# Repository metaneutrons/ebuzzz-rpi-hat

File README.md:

# eBuzzz adapter, an eBus to serial adapter

An eBus adapter, to convert eBus signal levels to serial level for a serial to USB converter (Works with CP2102)

# Manufacturing

Manufacturing in the `manufacturing` folder are made for JLCPCB, you may need to tweak them for other manufacturers.

# Software

The eBus protocol can be connected to with [ebusd](https://github.com/john30/ebusd). If you happen to use Home Assistant you can also connect ebusd to your Home Assistant.

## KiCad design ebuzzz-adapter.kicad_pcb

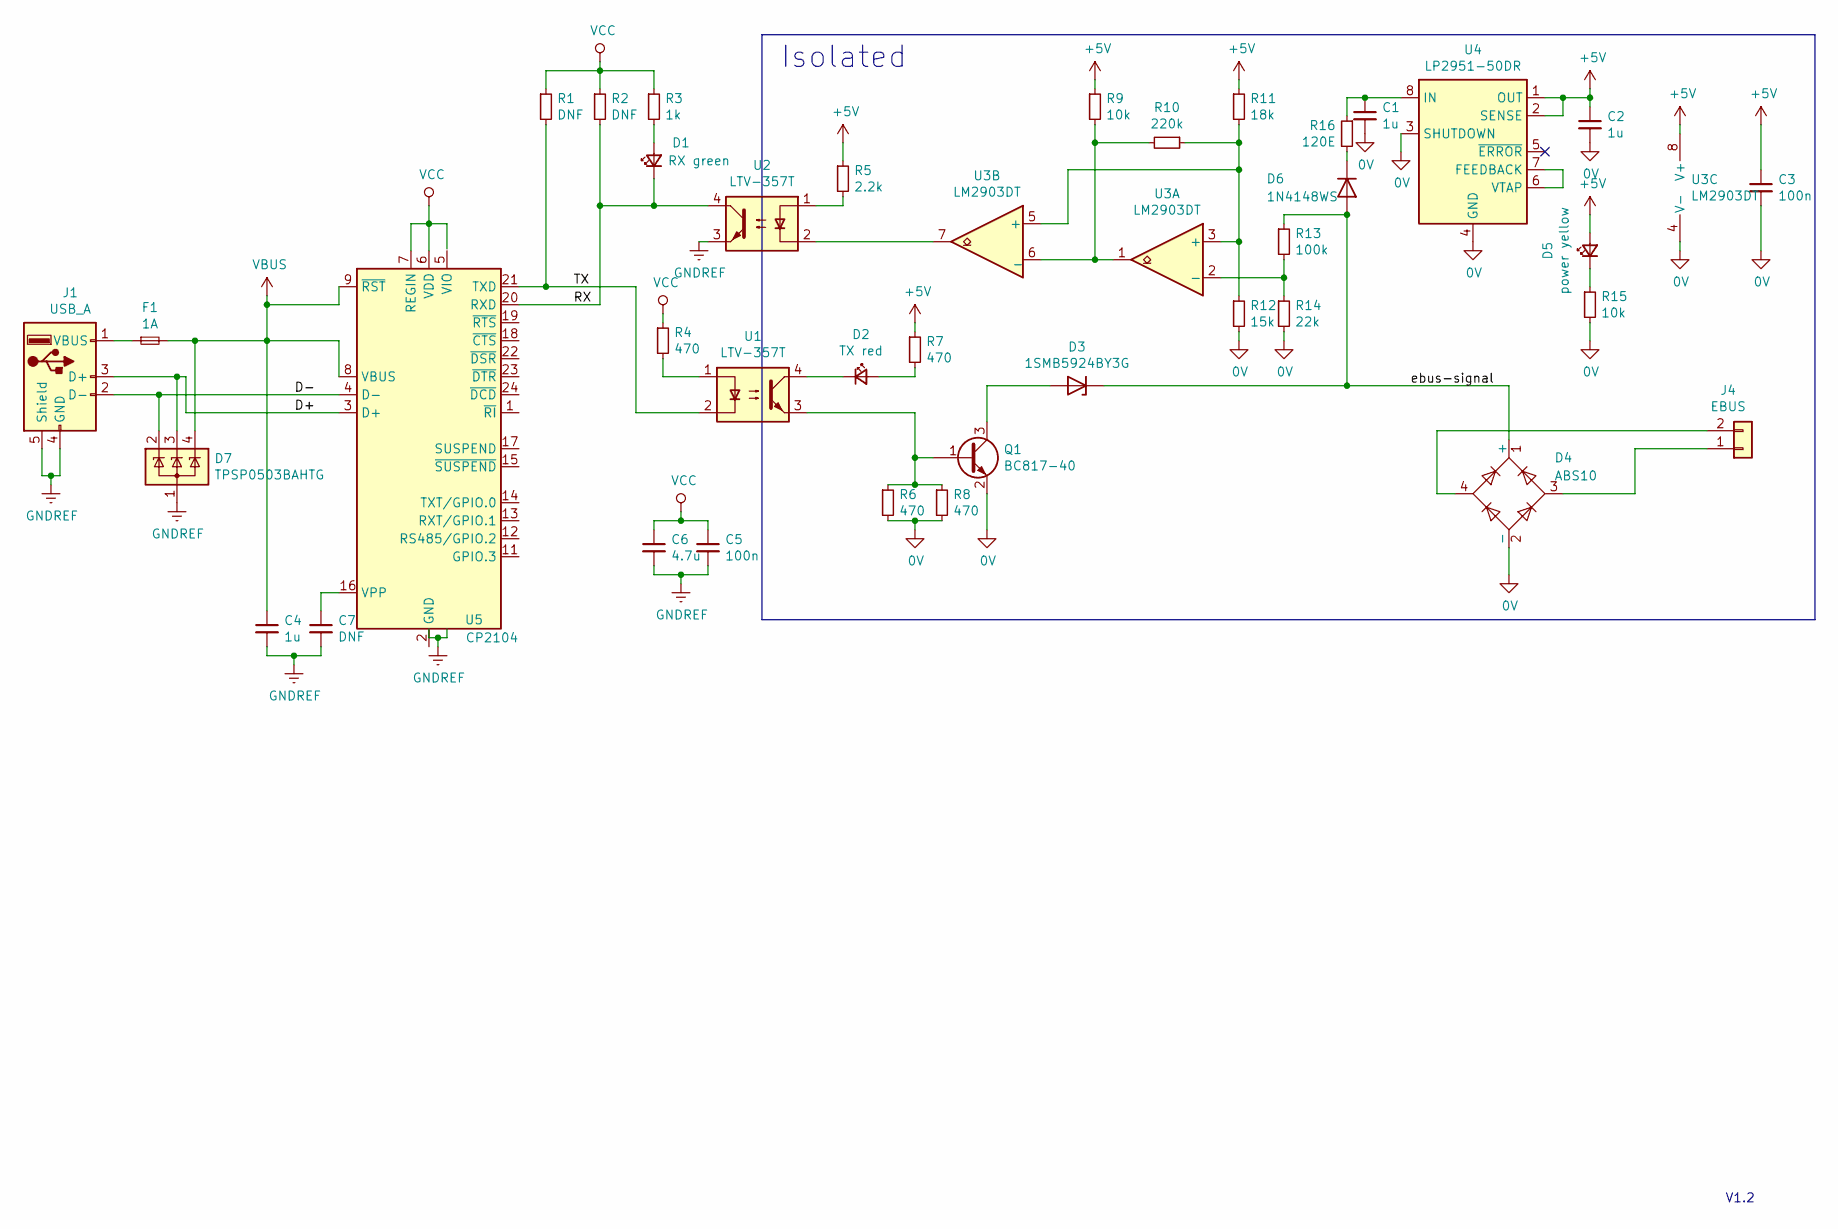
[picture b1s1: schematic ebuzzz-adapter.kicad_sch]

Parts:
C1, C2, C4: 1u; C_0805_2012Metric; LCSC C28323
C3, C5: 100n; C_0805_2012Metric; LCSC C49678
C6: 4.7u; C_0805_2012Metric; LCSC C1779
C7: DNF; C_0805_2012Metric
D1: RX green; LED_0805_2012Metric; LCSC C2297
D2: TX red; LED_0805_2012Metric; LCSC C84256
D3: 1SMB5924BY3G; D_SMA; Farnell 1611267
D4: ABS10; Diode_Bridge_Diotec_ABS; Farnell 3127182
D5: power yellow; LED_0805_2012Metric; LCSC C2296
D6: 1N4148WS; D_SOD-323; Farnell 2675148
D7: TPSP0503BAHTG; SOT-143; LCSC C2682275
F1: 1A; Fuse_1206_3216Metric; LCSC C182308
J1: USB_A; XKB_Connectivity_U217-041N-4BV81; LCSC C319178
J4: EBUS; PhoenixContact_MC_1,5_2-G-3.81_1x02_P3.81mm_Horizontal; LCSC C69811
Q1: BC817-40; SOT-23; Farnell 1798081
R1, R2: DNF; R_0805_2012Metric
R3: 1k; R_0805_2012Metric; LCSC C17513
R4, R6, R7, R8: 470; R_0805_2012Metric; LCSC C17710
R5: 2.2k; R_0805_2012Metric; LCSC C17520
R9, R15: 10k; R_0805_2012Metric; LCSC C17414
R10: 220k; R_0805_2012Metric; LCSC C17556
R11: 18k; R_0805_2012Metric; LCSC C17506
R12: 15k; R_0805_2012Metric; LCSC C17475
R13: 100k; R_0805_2012Metric; LCSC C17407
R14: 22k; R_0805_2012Metric; LCSC C17560
R16: 120E; R_0805_2012Metric; LCSC C17437
U1, U2: LTV-357T; SO-4_4.4x3.6mm_P2.54mm; LCSC C33068
U3: LM2903DT; SOIC-8_3.9x4.9mm_P1.27mm; Farnell 2382615
U4: LP2951-50DR; SOIC-8_3.9x4.9mm_P1.27mm; Farnell 1755065
U5: CP2104; QFN-24-1EP_4x4mm_P0.5mm_EP2.6x2.6mm_ThermalVias; LCSC C47742

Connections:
+5V: C2.1, C3.1, D5.2 (A), R5.1, R7.1, R9.1, R11.1, U3.8 (V+), U4.1 (OUT), U4.2 (SENSE)
/D+: D7.3 (K), J1.3 (D+), U5.3 (D+)
/D-: D7.2 (K), J1.2 (D-), U5.4 (D-)
/RX: D1.1 (K), R2.2, U2.4, U5.20 (RXD)
/TX: R1.2, U1.2, U5.21 (TXD)
/ebus-signal: D3.1 (K), D4.1 (+), D6.2 (A), R13.1
GND: C1.2, C2.2, C3.2, D4.2 (-), Q1.2 (E), R6.2, R8.2, R12.2, R14.2, R15.2, U3.4 (V-), U4.3 (SHUTDOWN), U4.4 (GND)
GNDREF: C4.2, C5.2, C6.2, C7.2, D7.1 (A), J1.4 (GND), J1.5 (Shield), U2.3
unnamed: C1.1, R16.1, U4.8 (IN)
unnamed: C7.1, U5.16 (VPP)
unnamed: D1.2 (A), R3.2
unnamed: D2.1 (K), U1.4
unnamed: D2.2 (A), R7.2
unnamed: D3.2 (A), Q1.3 (C)
unnamed: D4.3, J4.1
unnamed: D4.4, J4.2
unnamed: D5.1 (K), R15.1
unnamed: D6.1 (K), R16.2
unnamed: F1.1, J1.1 (VBUS)
unnamed: Q1.1 (B), R6.1, R8.1, U1.3
unnamed: R4.2, U1.1
unnamed: R5.2, U2.1
unnamed: R10.1, R11.2, R12.1, U3.3 (+), U3.5 (+)
unnamed: R9.2, R10.2, U3.1, U3.6 (_)
unnamed: R13.2, R14.1, U3.2 (-)
unnamed: U2.2, U3.7
unnamed: U4.6 (VTAP), U4.7 (FEEDBACK)
unnamed: U5.2 (GND), U5.25 (GND)
VBUS: C4.1, D7.4 (K), F1.2, U5.8 (VBUS), U5.9 (~RST)
VCC: C5.1, C6.1, R1.1, R2.1, R3.1, R4.1, U5.6 (VDD), U5.7 (REGIN)

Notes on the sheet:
Isolated
V1.2

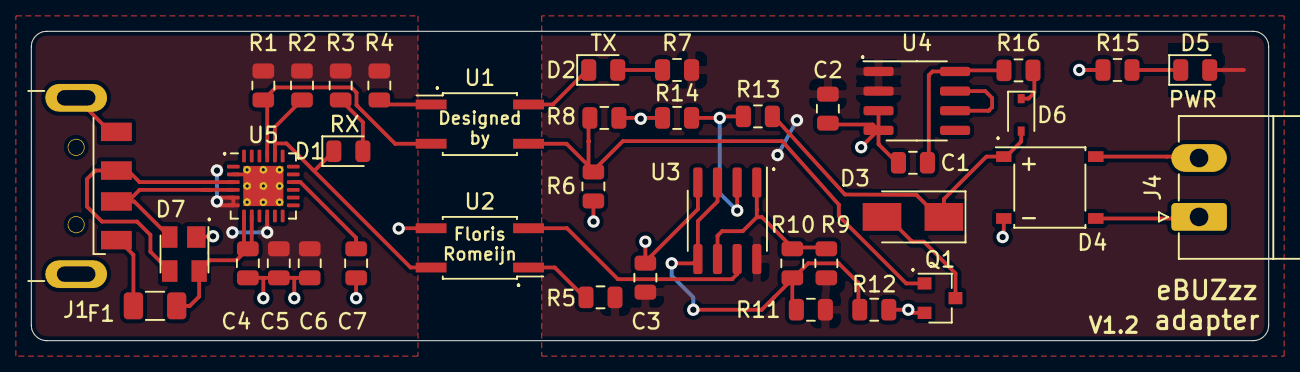
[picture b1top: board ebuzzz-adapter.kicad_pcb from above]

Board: 2 copper layers, 80.0 x 20.0 mm, 39 parts (0 on the bottom side), 30 nets.

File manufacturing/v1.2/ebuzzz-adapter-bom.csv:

Designator,Comment,Footprint,LCSC
C1,1u,Capacitor_SMD:C_0805_2012Metric,C28323
C2,1u,Capacitor_SMD:C_0805_2012Metric,C28323
C3,100n,Capacitor_SMD:C_0805_2012Metric,C49678
C4,1u,Capacitor_SMD:C_0805_2012Metric,C28323
C5,100n,Capacitor_SMD:C_0805_2012Metric,C49678
C6,4.7u,Capacitor_SMD:C_0805_2012Metric,C1779
D1,RX green,LED_SMD:LED_0805_2012Metric,C2297
D2,TX red,LED_SMD:LED_0805_2012Metric,C84256
D3,1SMB5924BY3G,Diode_SMD:D_SMA,C53166
D4,ABS10,Diode_SMD:Diode_Bridge_Diotec_ABS,C65028
D5,power yellow,LED_SMD:LED_0805_2012Metric,C2296
D6,1N4148WS,Diode_SMD:D_SOD-323,C57759
D7,TPSP0503BAHTG,Package_TO_SOT_SMD:SOT-143,C2682275
F1,1A,Fuse:Fuse_1206_3216Metric,C182308
Q1,BC817-40,Package_TO_SOT_SMD:SOT-23,C181151
R3,1k,Resistor_SMD:R_0805_2012Metric,C17513
R4,470,Resistor_SMD:R_0805_2012Metric,C17710
R5,2.2k,Resistor_SMD:R_0805_2012Metric,C17520
R6,470,Resistor_SMD:R_0805_2012Metric,C17710
R7,470,Resistor_SMD:R_0805_2012Metric,C17710
R8,470,Resistor_SMD:R_0805_2012Metric,C17710
R9,10k,Resistor_SMD:R_0805_2012Metric,C17414
R10,220k,Resistor_SMD:R_0805_2012Metric,C17556
R11,18k,Resistor_SMD:R_0805_2012Metric,C17506
R12,15k,Resistor_SMD:R_0805_2012Metric,C17475
R13,100k,Resistor_SMD:R_0805_2012Metric,C17407
R14,22k,Resistor_SMD:R_0805_2012Metric,C17560
R15,10k,Resistor_SMD:R_0805_2012Metric,C17414
R16,120E,Resistor_SMD:R_0805_2012Metric,C17437
U1,LTV-357T,Package_SO:SO-4_4.4x3.6mm_P2.54mm,C33068
U2,LTV-357T,Package_SO:SO-4_4.4x3.6mm_P2.54mm,C33068
U3,LM2903DT,Package_SO:SOIC-8_3.9x4.9mm_P1.27mm,C98194
U4,LP2951-50DR,Package_SO:SOIC-8_3.9x4.9mm_P1.27mm,C109380
U5,CP2104-F03-GM,Package_DFN_QFN:QFN-24-1EP_4x4mm_P0.5mm_EP2.6x2.6mm_ThermalVias,C430013
J4,EBUS,Connector_Phoenix_MC:PhoenixContact_MC_1.5_2-G-3.81_1x02_P3.81mm_Horizontal,C69811
J1,USB A,Connector_USB:USB_A_CNCTech_1001-011-01101_Horizontal,C319178

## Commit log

2019-10-25 Version 1 release (hardware tested)
2020-08-11 added schematic as pdf
2020-11-12 added LCSC components (and tuned values)
2020-12-10 replace external board with onboard CP2104
2021-11-19 added manufacturing files
2022-01-09 Changed project to KiCad 6.0 format.
2022-01-09 Fixed schematics after KiCad 6.0 upgrade.
2022-01-09 Updated PCB.
